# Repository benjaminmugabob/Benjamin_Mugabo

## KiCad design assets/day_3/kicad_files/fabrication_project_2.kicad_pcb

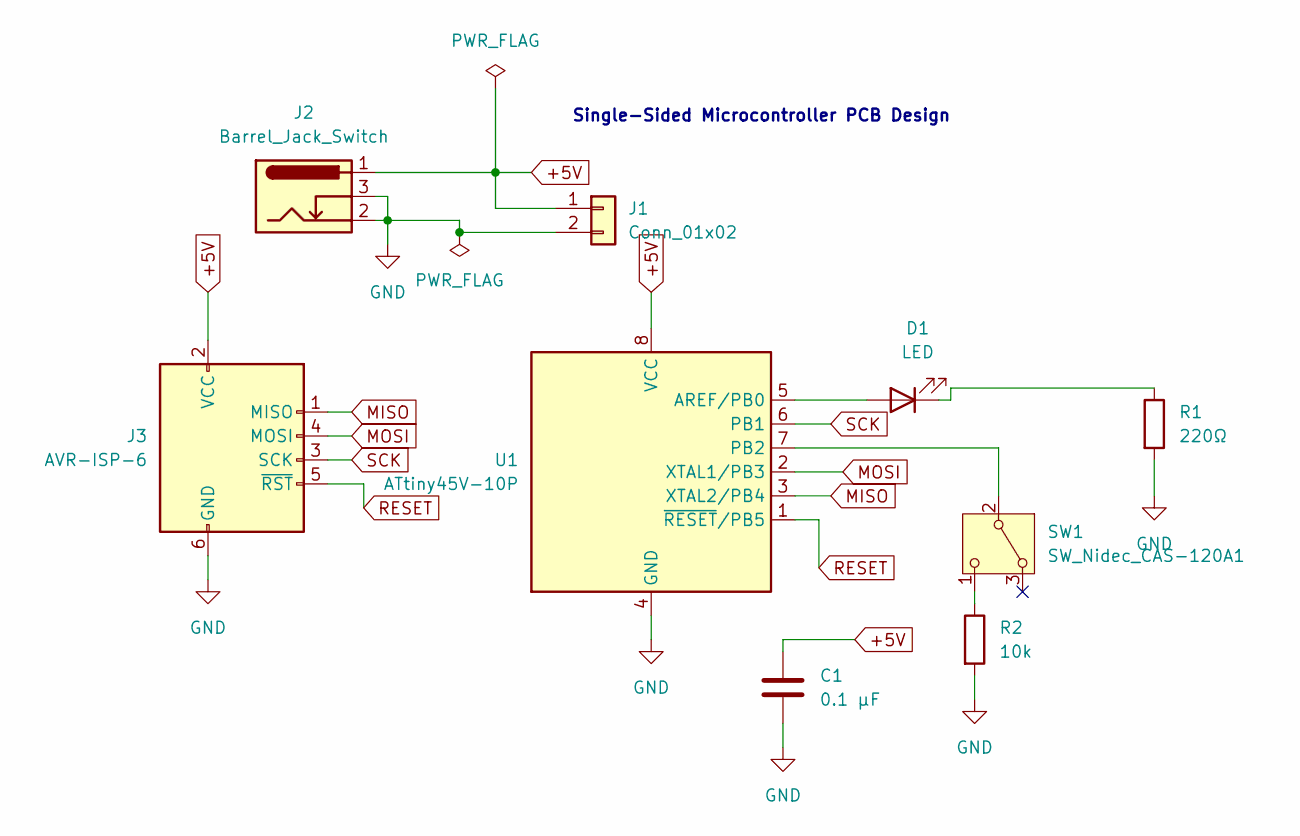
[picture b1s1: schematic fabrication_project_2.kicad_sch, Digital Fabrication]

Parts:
C1: 0.1 µF; CP_Elec_3x5.3
D1: LED; CP_Axial_L55.0mm_D23.0mm_P60.00mm_Horizontal
J1: Conn_01x02; PinHeader_1x02_P1.00mm_Vertical
J2: Barrel_Jack_Switch; BarrelJack_Horizontal
J3: AVR-ISP-6; PinHeader_2x03_P2.00mm_Vertical
R1: 220Ω; R_Axial_DIN0204_L3.6mm_D1.6mm_P5.08mm_Horizontal
R2: 10k; R_Axial_DIN0204_L3.6mm_D1.6mm_P5.08mm_Horizontal
SW1: SW_Nidec_CAS-120A1; Nidec_Copal_CAS-120A
U1: ATtiny45V-10P; DIP-8_W7.62mm

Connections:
+5V: C1.1, J1.1, J2.1, J3.2 (VCC), U1.8 (VCC)
GND: C1.2, J1.2, J2.2, J2.3, J3.6 (GND), R1.2, R2.2, U1.4 (GND)
MISO: J3.1 (MISO), U1.3 (XTAL2/PB4)
MOSI: J3.4 (MOSI), U1.2 (XTAL1/PB3)
unnamed: D1.2 (A), U1.5 (AREF/PB0)
unnamed: D1.1 (K), R1.1
unnamed: SW1.2 (B), U1.7 (PB2)
unnamed: R2.1, SW1.1 (C)
RESET: J3.5 (~RST), U1.1 (~RESET/PB5)
SCK: J3.3 (SCK), U1.6 (PB1)

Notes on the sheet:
Single-Sided Microcontroller PCB Design

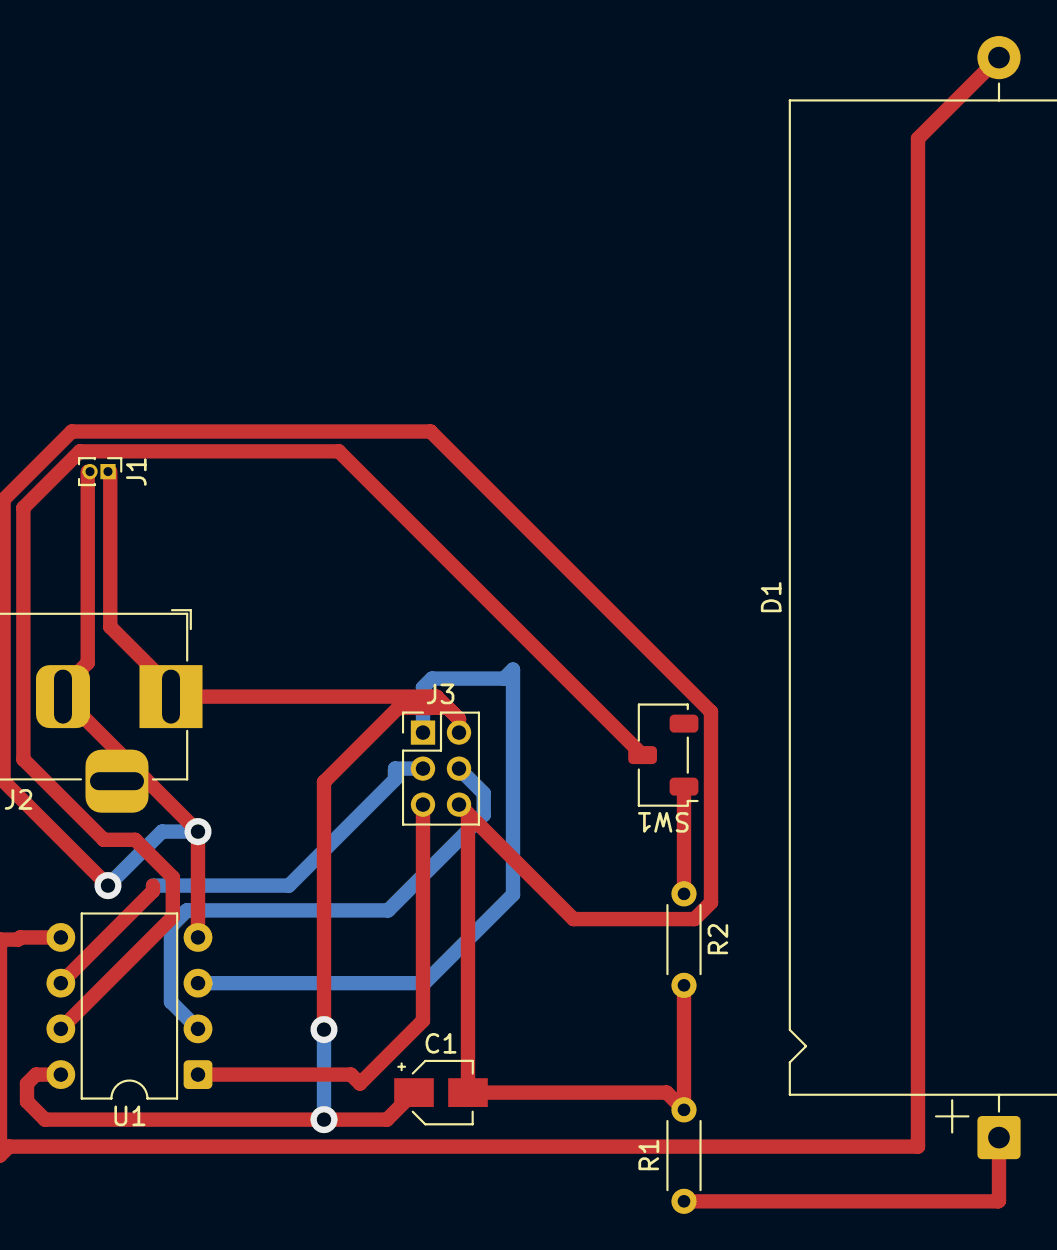
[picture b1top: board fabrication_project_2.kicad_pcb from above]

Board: 2 copper layers, 9 parts (0 on the bottom side), 10 nets.

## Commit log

2026-01-30 Initial MkDocs project for Modeling Fabrication Technique
2026-01-30 Deployed e3bd97d with MkDocs version: 1.6.1
2026-04-07 Updating the works done
2026-04-07 Deployed 2a43146 with MkDocs version: 1.6.1
2026-04-07 Update the documents
2026-04-07 Deployed c5ee40f with MkDocs version: 1.6.1
